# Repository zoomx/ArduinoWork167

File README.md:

# ArduinoWork167
Arduino sketches

Various Arduino Sketches

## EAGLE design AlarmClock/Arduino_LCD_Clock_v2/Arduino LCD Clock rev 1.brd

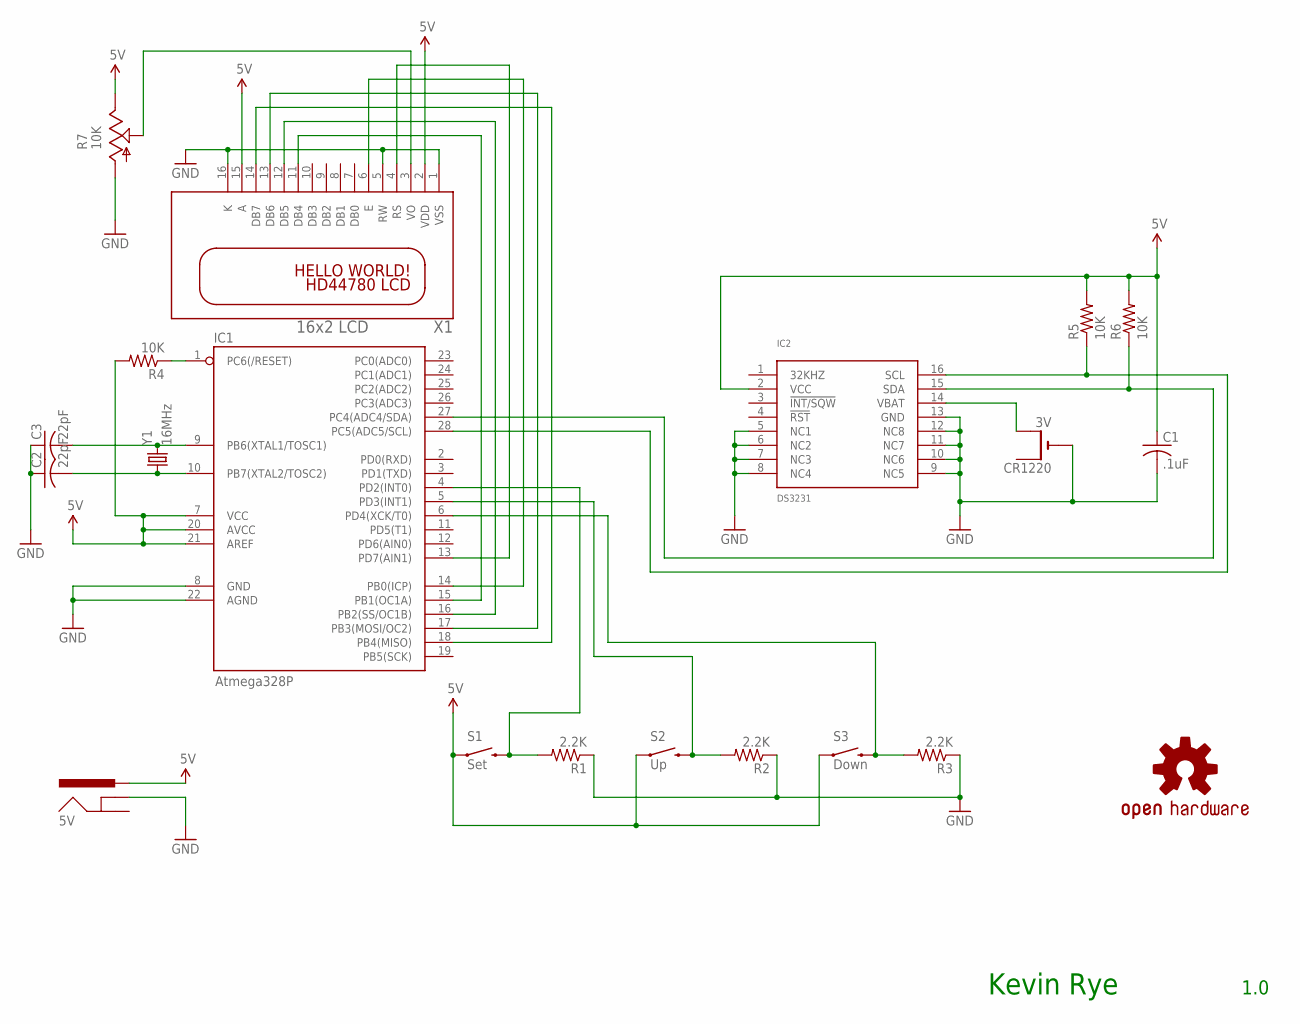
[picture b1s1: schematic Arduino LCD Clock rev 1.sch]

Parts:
5V: POWER_JACKSLT; POWER_JACK_SLOT
C1: .1uF; C025-024X044
C2, C3: 22pF; C025-024X044
CR1220: 3V; CR1220-THM
IC1: Atmega328P; DIL28-3
IC2: DS3231; SO16W
R1, R2, R3: 2.2K; AXIAL-0.4
R4, R5, R6: 10K; AXIAL-0.4
R7: 10K; S63S
S1: Set; TACTILE-PTH-12MM
S2: Up; TACTILE-PTH-12MM
S3: Down; TACTILE-PTH-12MM
U$2: OSHW-LOGOM; OSHW-LOGO-M
X1: 16x2 LCD; LCD1602
Y1: 16MHz; HC49US

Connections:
5V: 5V.PWR, C1.1, IC1.7 (VCC), IC1.20 (AVCC), IC1.21 (AREF), IC2.2 (VCC), R4.P$2 (2), R5.P$2 (2), R6.P$2 (2), R7.E, S1.1, S2.1, S3.1, X1.2 (VDD), X1.15 (A)
GND: 5V.GND@1 (GNDBREAK), C1.2, C2.1, C3.1, CR1220.-, IC1.8 (GND), IC1.22 (AGND), IC2.5 (NC1), IC2.6 (NC2), IC2.7 (NC3), IC2.8 (NC4), IC2.9 (NC5), IC2.10 (NC6), IC2.11 (NC7), IC2.12 (NC8), IC2.13 (GND), R1.P$1 (1), R2.P$1 (1), R3.P$1 (1), R7.A, X1.1 (VSS), X1.5 (RW), X1.16 (K)
unnamed: CR1220.+2 (+1), IC2.14 (VBAT)
unnamed: IC1.18 (PB4(MISO)), X1.14 (DB7)
unnamed: IC1.17 (PB3(MOSI/OC2)), X1.13 (DB6)
unnamed: IC1.28 (PC5(ADC5/SCL)), IC2.16 (SCL), R5.P$1 (1)
unnamed: IC1.13 (PD7(AIN1)), X1.4 (RS)
unnamed: C3.2, IC1.9 (PB6(XTAL1/TOSC1)), Y1.2
unnamed: C2.2, IC1.10 (PB7(XTAL2/TOSC2)), Y1.1
unnamed: IC1.1 (PC6(/RESET)), R4.P$1 (1)
unnamed: R7.S, X1.3 (VO)
unnamed: IC1.14 (PB0(ICP)), X1.6 (E)
unnamed: IC1.16 (PB2(SS/OC1B)), X1.12 (DB5)
unnamed: IC1.15 (PB1(OC1A)), X1.11 (DB4)
unnamed: IC1.5 (PD3(INT1)), R2.P$2 (2), S2.3 (2)
unnamed: IC1.27 (PC4(ADC4/SDA)), IC2.15 (SDA), R6.P$1 (1)
unnamed: IC1.4 (PD2(INT0)), R1.P$2 (2), S1.3 (2)
unnamed: IC1.6 (PD4(XCK/T0)), R3.P$2 (2), S3.3 (2)

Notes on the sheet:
1.0
Kevin Rye

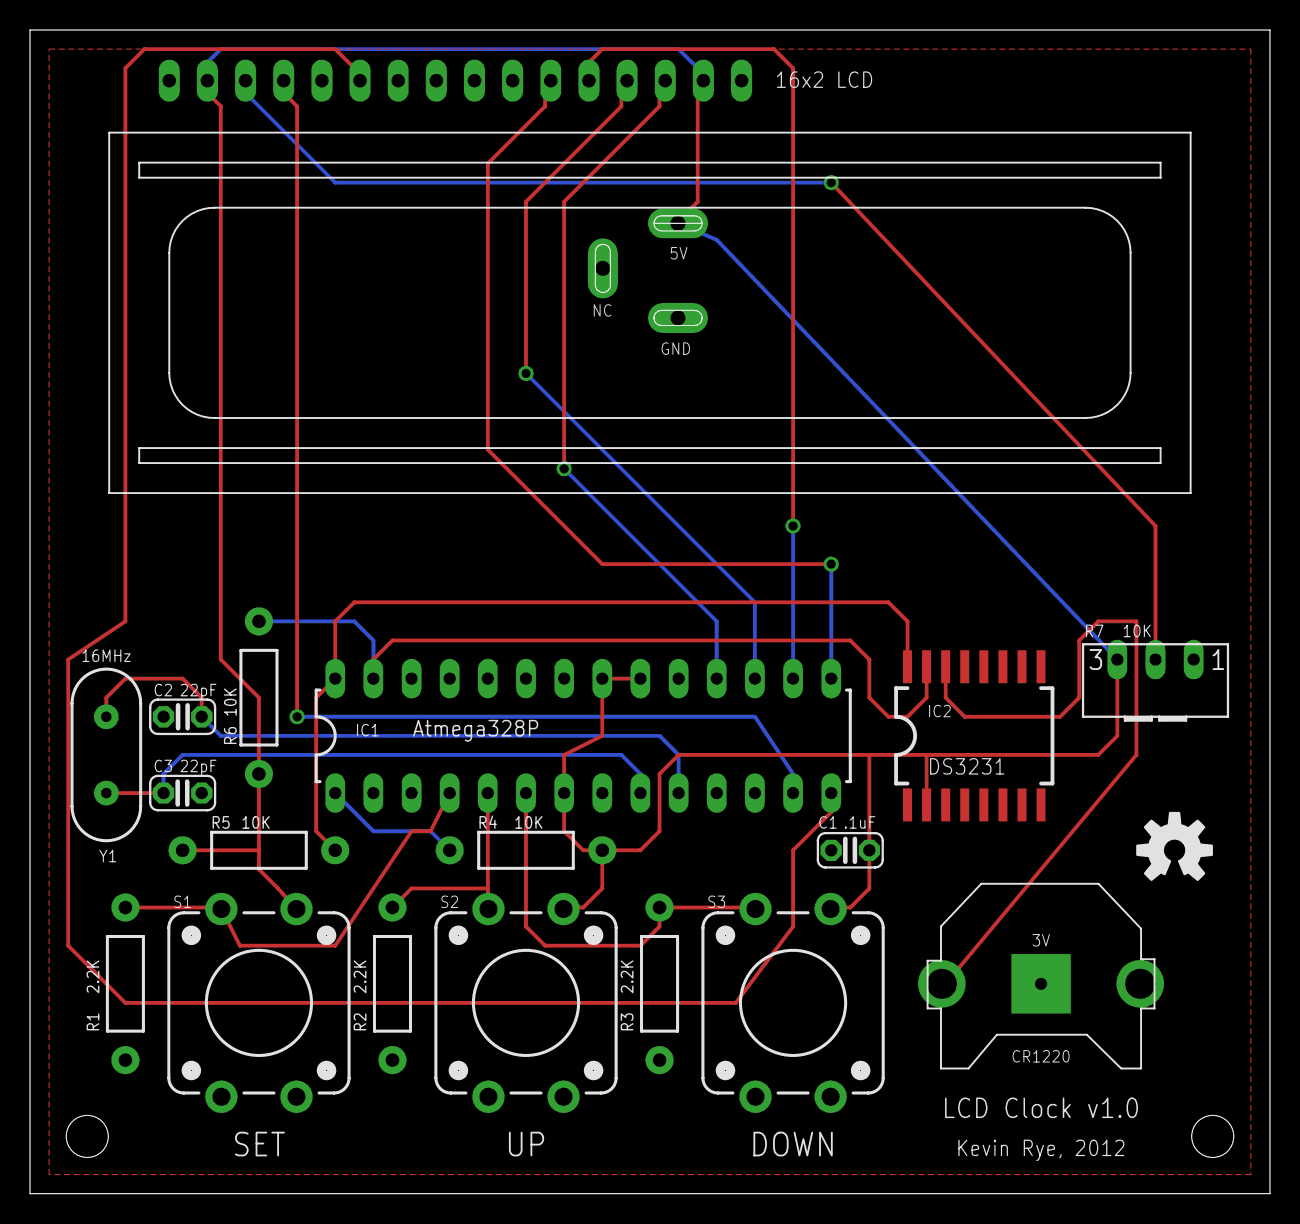
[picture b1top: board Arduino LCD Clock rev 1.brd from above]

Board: 2 copper layers, 82.5 x 77.5 mm, 20 parts (1 on the bottom side), 18 nets.

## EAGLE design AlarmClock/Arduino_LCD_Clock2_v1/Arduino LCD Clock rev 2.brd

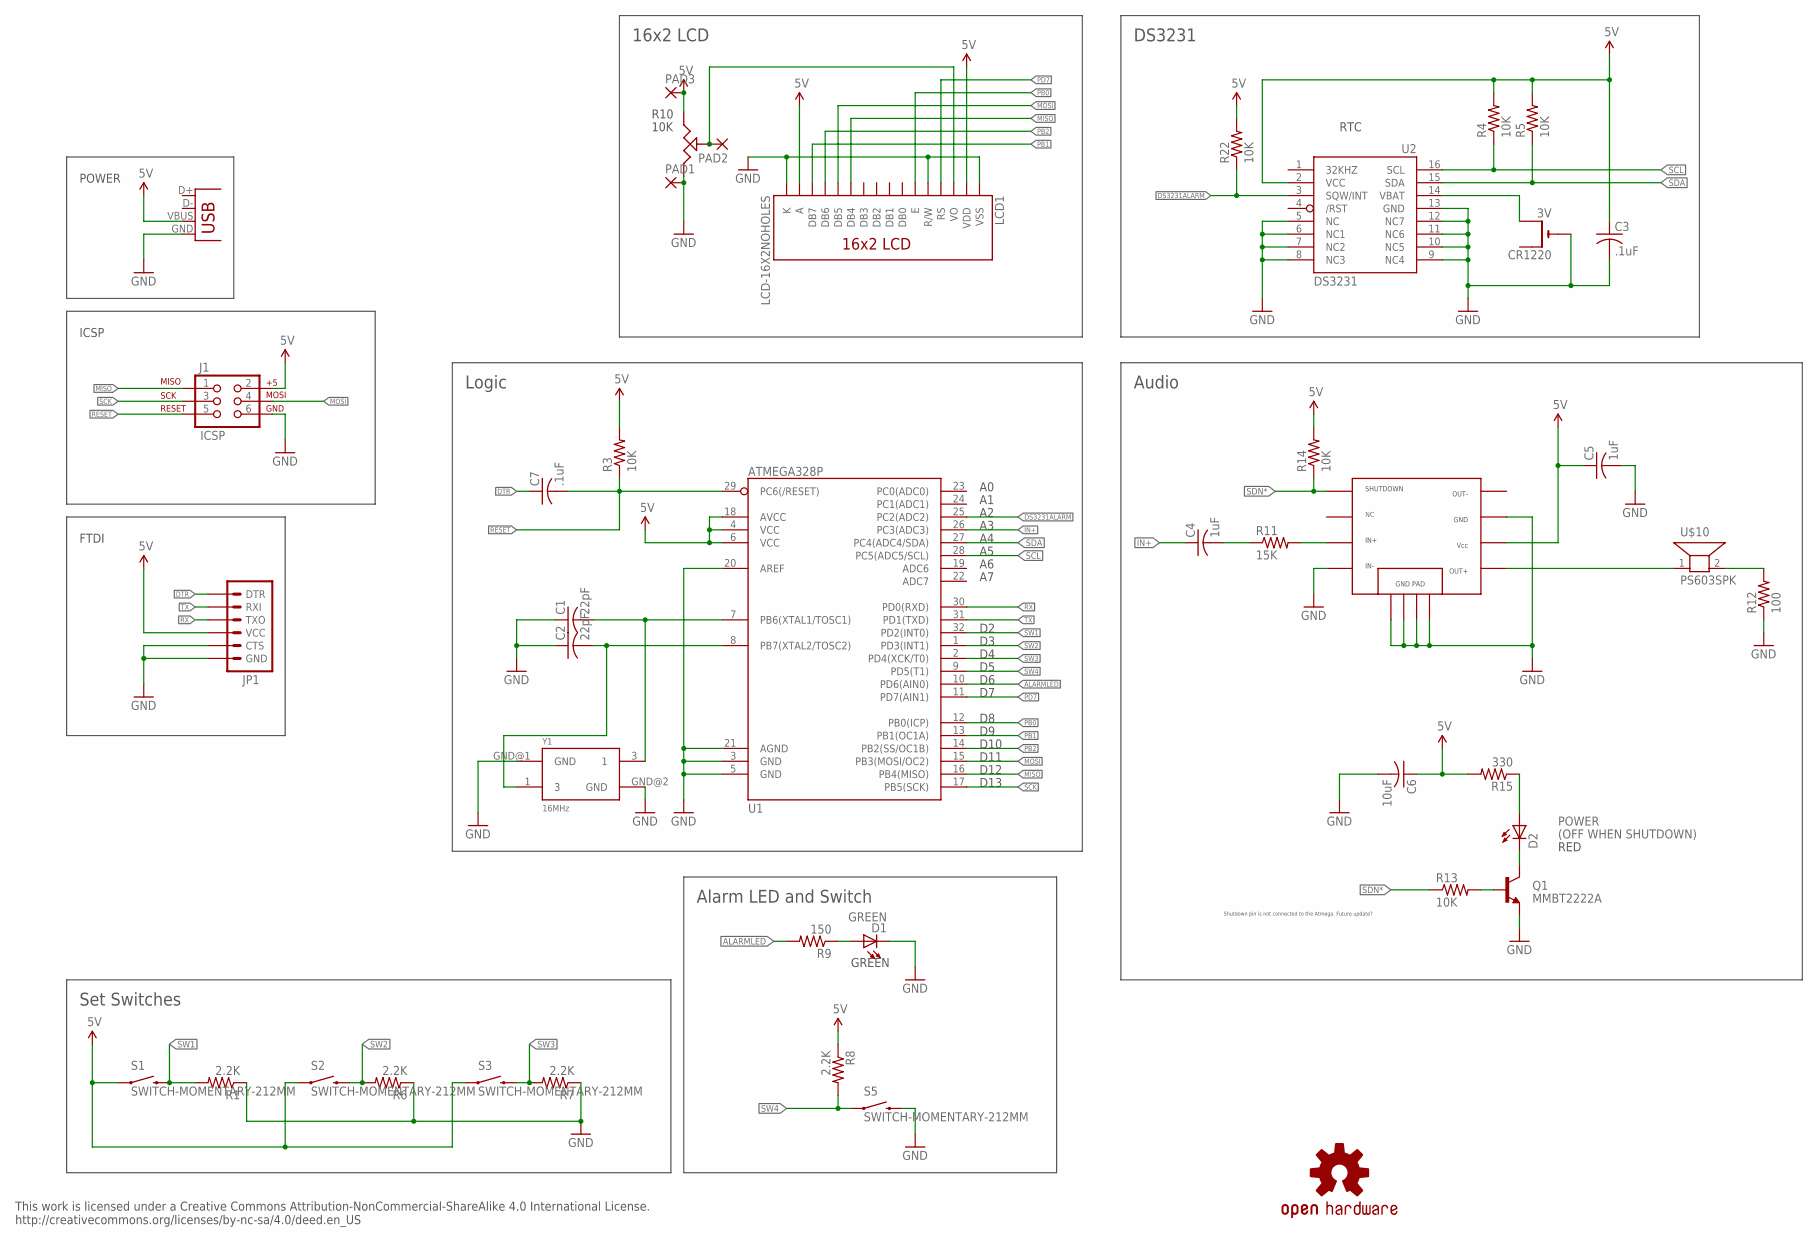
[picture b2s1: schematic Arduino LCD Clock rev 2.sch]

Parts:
C1, C2: 22pF; C0805K
C3, C7: .1uF; C0805K
C4, C5: 1uF; C0805K
C6: 10uF; C0805K
CR1220: 3V; CR1220-THM
D1: GREEN; LED-1206
D2: LED-RED1206; LED-1206
J1: ICSP; 2X3
JP1: ARDUINO_SERIAL_PROGRAMSMD; 1X06-SMD
JP3: (POWER ONLY); USB-B-PTH-VERTICAL
LCD1: LCD-16X2NOHOLES; LCD-16X2_NOHOLES
PAD1, PAD2, PAD3: SMD2; SMD1,27-2,54
Q1: MMBT2222A; SOT23-3
R1, R6, R7, R8: 2.2K; R0805
R3, R4, R5, R13, R14, R22: 10K; R0805
R9: 150; R0805
R11: 15K; R0805
R12: 100; R0805
R15: 330; R0805
S1, S2, S3, S5: SWITCH-MOMENTARY-212MM; TACTILE-PTH-12MM
U1: ATMEGA328P; TQFP32-08
U2: DS3231; SO16W
U3: TPA2005; MSOP8
U$2: OSHW-LOGOM; OSHW-LOGO-M
U$6: PVG3A103C01R00_TRIMPOT
U$10: PS603SPK; PS603
Y1: 16MHz; CRYSTAL-SMD-5X3

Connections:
5V: C3.1, C5.1, C6.1, J1.2, JP1.4 (VCC), JP3.VBUS, LCD1.2 (VDD), LCD1.15 (A), PAD3.1, R3.2, R4.2, R5.2, R8.1, R14.2, R15.2, R22.2, S1.1, S2.1, S3.1, U1.4 (VCC), U1.6 (VCC), U1.18 (AVCC), U2.2 (VCC), U3.6, U$6.1 (IN), U$6.1$ (IN)
ALARMLED: R9.2, U1.10 (PD6(AIN0))
DS3231ALARM: R22.1, U1.25 (PC2(ADC2)), U2.3 (SQW/INT)
DTR: C7.1, JP1.1 (DTR)
GND: C1.1, C2.1, C3.2, C5.2, C6.2, CR1220.-, D1.C, J1.6, JP1.5 (CTS), JP1.6 (GND), JP3.GND, LCD1.1 (VSS), LCD1.5 (R/W), LCD1.16 (K), PAD1.1, Q1.2 (E), R1.1, R6.1, R7.1, R12.1, S5.3 (2), U1.3 (GND), U1.5 (GND), U1.20 (AREF), U1.21 (AGND), U2.5 (NC), U2.6 (NC1), U2.7 (NC2), U2.8 (NC3), U2.9 (NC4), U2.10 (NC5), U2.11 (NC6), U2.12 (NC7), U2.13 (GND), U3.4, U3.7, U3.A, U3.B, U3.C, U3.D, U$6.3 (GND), U$6.3$ (GND), Y1.GND@1 (GND), Y1.GND@2 (GND)
IN+: C4.1, U1.26 (PC3(ADC3))
IN+AMP: R11.2, U3.3
MISO: J1.1, LCD1.11 (DB4), U1.16 (PB4(MISO))
MOSI: J1.4, LCD1.12 (DB5), U1.15 (PB3(MOSI/OC2))
unnamed: CR1220.+2 (+1), U2.14 (VBAT)
unnamed: U3.5, U$10.1
unnamed: LCD1.3 (VO), PAD2.1, U$6.2 (OUT), U$6.2! (OUT)
unnamed: R12.2, U$10.2
unnamed: D1.A, R9.1
unnamed: D2.A, R15.1
unnamed: Q1.1 (B), R13.2
unnamed: D2.C, Q1.3 (C)
unnamed: C4.2, R11.1
unnamed: C1.2, U1.7 (PB6(XTAL1/TOSC1)), Y1.3 (1)
unnamed: C2.2, U1.8 (PB7(XTAL2/TOSC2)), Y1.1 (3)
PB0: LCD1.6 (E), U1.12 (PB0(ICP))
PB1: LCD1.14 (DB7), U1.13 (PB1(OC1A))
PB2: LCD1.13 (DB6), U1.14 (PB2(SS/OC1B))
PD7: LCD1.4 (RS), U1.11 (PD7(AIN1))
RESET: C7.2, J1.5, R3.1, U1.29 (PC6(/RESET))
RX: JP1.3 (TXO), U1.30 (PD0(RXD))
SCK: J1.3, U1.17 (PB5(SCK))
SCL: R4.1, U1.28 (PC5(ADC5/SCL)), U2.16 (SCL)
SDA: R5.1, U1.27 (PC4(ADC4/SDA)), U2.15 (SDA)
SDN*: R13.1, R14.1, U3.1
SW1: R1.2, S1.3 (2), U1.32 (PD2(INT0))
SW2: R6.2, S2.3 (2), U1.1 (PD3(INT1))
SW3: R7.2, S3.3 (2), U1.2 (PD4(XCK/T0))
SW4: R8.2, S5.1, U1.9 (PD5(T1))
TX: JP1.2 (RXI), U1.31 (PD1(TXD))

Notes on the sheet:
RTC
POWER
(OFF WHEN SHUTDOWN)
Audio
Set Switches
DS3231
Alarm LED and Switch
16x2 LCD
FTDI
ICSP
D10
D11
D12
D13
Logic
GREEN
RED
10K
R10
This work is licensed under a Creative Commons Attribution-NonCommercial-ShareAlike 4.0 International License. http://creativecommons.org/licenses/by-nc-sa/4.0/deed.en_US
Shutdown pin is not connected to the Atmega. Future update?

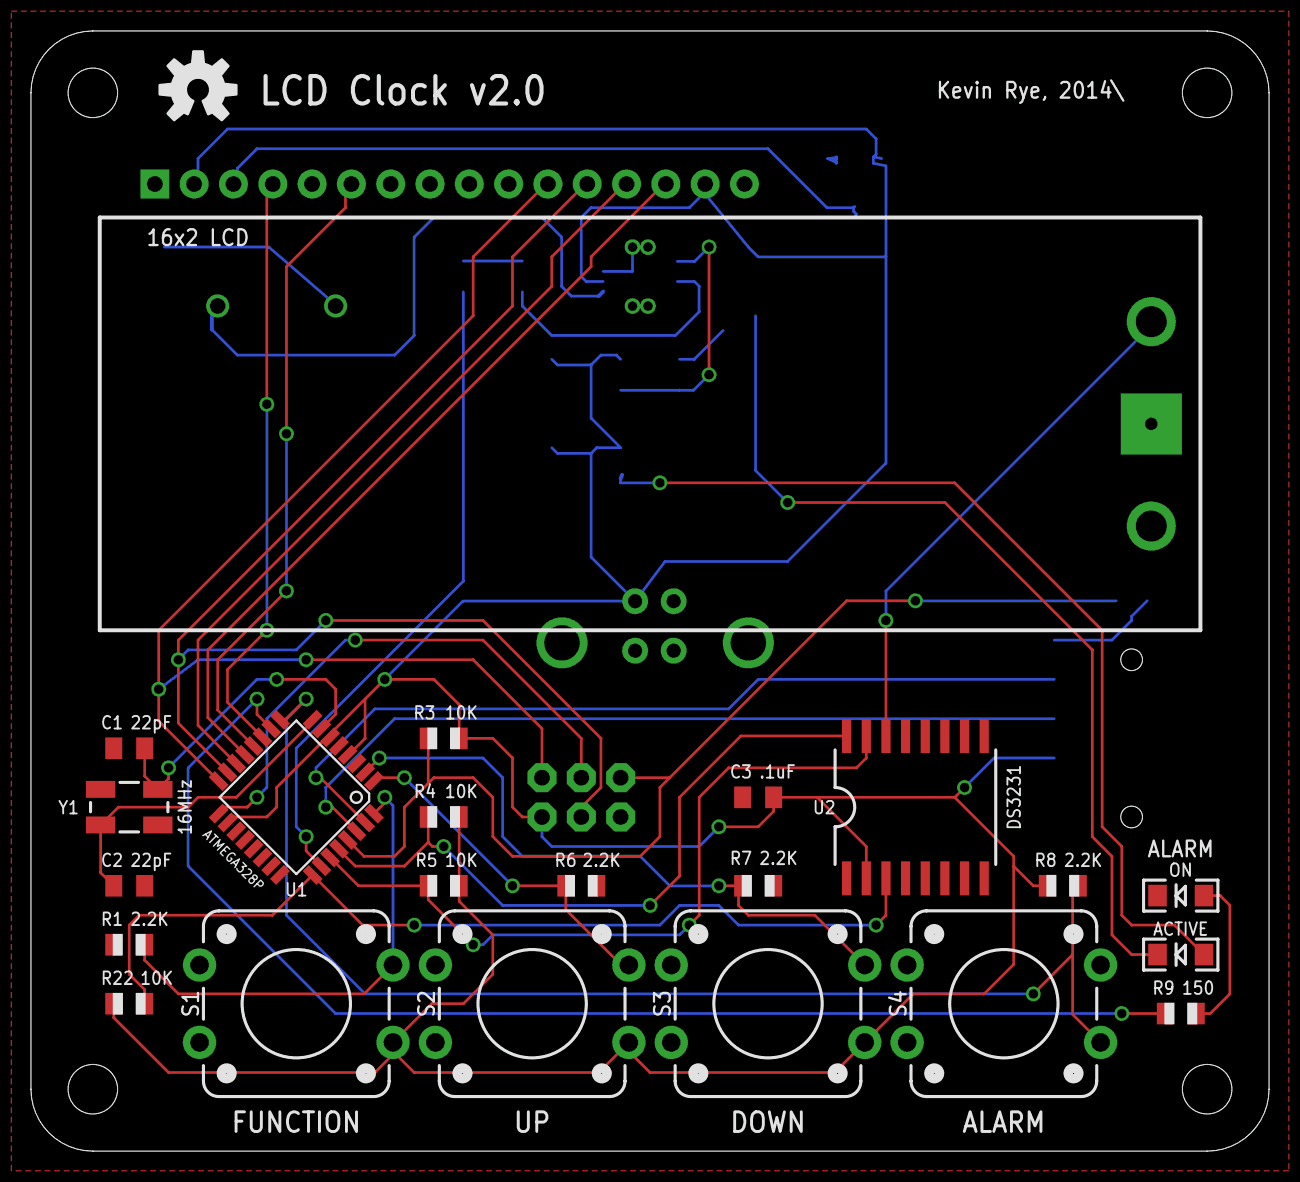
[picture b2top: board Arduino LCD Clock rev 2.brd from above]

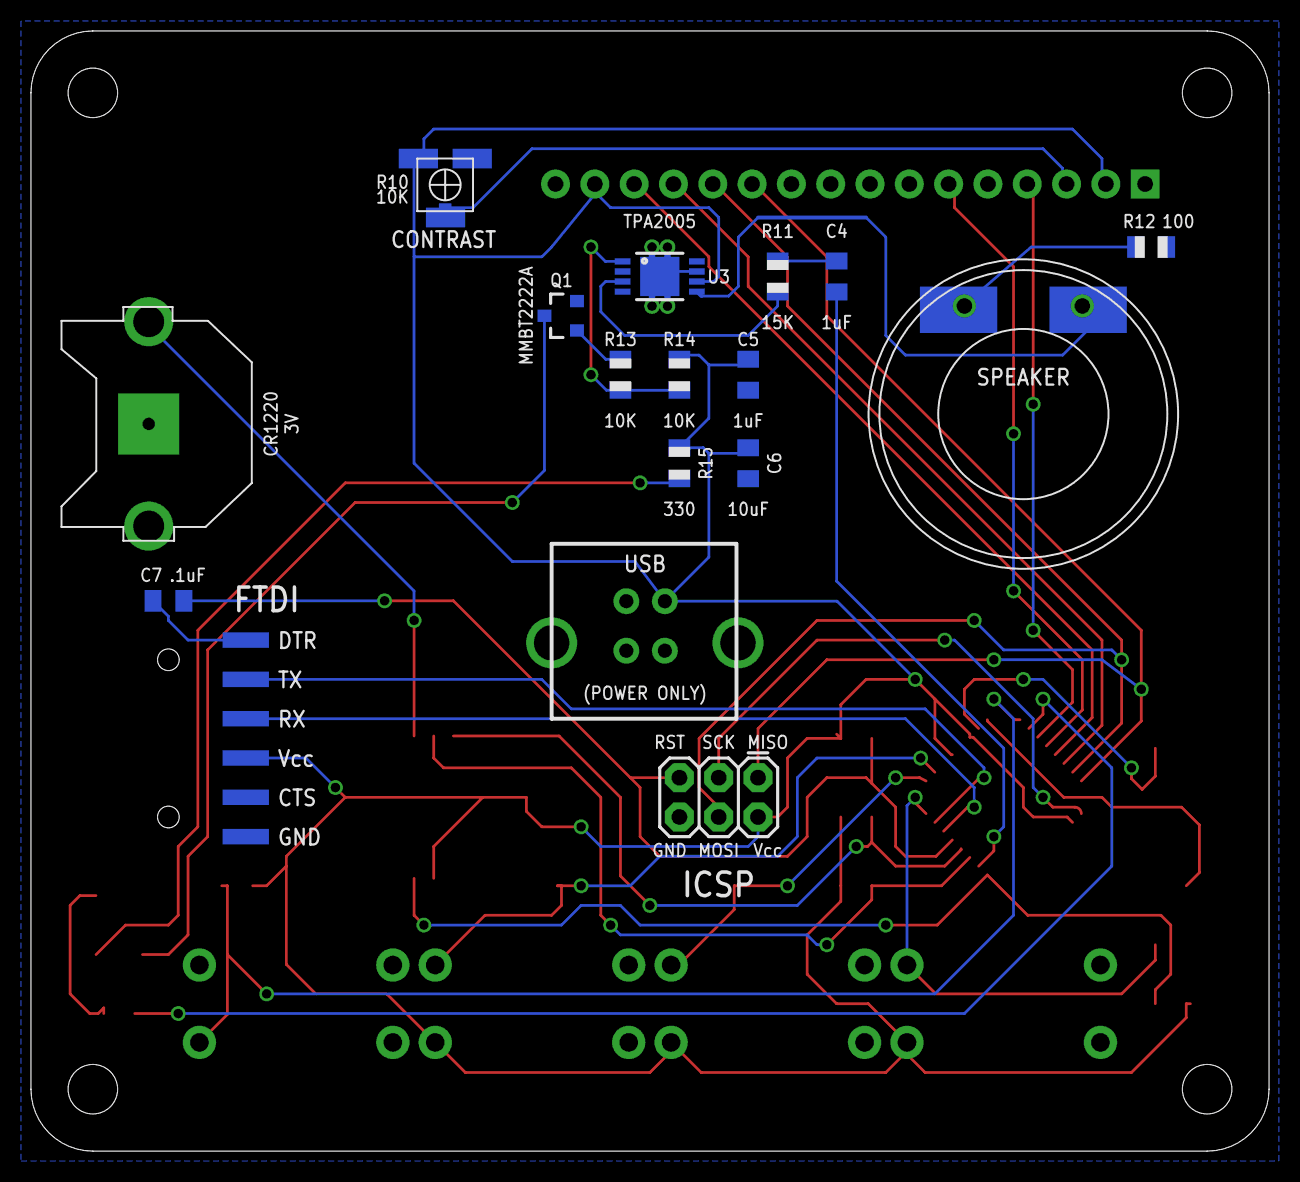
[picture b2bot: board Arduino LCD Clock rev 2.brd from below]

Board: 2 copper layers, 80.0 x 72.4 mm, 44 parts (20 on the bottom side), 35 nets.

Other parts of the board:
U$5: LCD_V2_FOOTPRINT

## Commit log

2016-03-10 Added files via upload
2016-03-10 Added libraries
2016-03-14 Added some comments
2016-03-15 Software serial pins changed
    Software serial pins changed to 2 and 3
2016-03-17 Initial code
2016-03-17 Some changes but no voice
2016-03-18 Added comment that doesn't work
    Doesn't work because PCM is on Pin 11 used by MISO for SPI communication with Ethernet card
2016-03-18 This one works.
2016-03-21 Added Alarm
    Added an alarm when CO2 is more than a value. Some libraries are now in the same sketch folder.
2016-07-22 Add files via upload
    Added NRF24Sensors Sketches
2016-10-20 Added one shield test
    Added Quad_Relay_Shield_test
2016-10-21 Original Rude Bastard Sketch
    taken from http://www.rudebastard.com/article.php?story=20130310155336385
2016-10-21 My modifications
    My modifications
2016-10-21 Now 0 mean relay off
    Changed the logic since in the original sketch was negate
    Now 0 mean relay off
2016-10-21 Corrected silly error on readme
    logis is now logic!
2016-10-21 Added mask and gateway for fixed IP
2016-11-02 First version
2016-11-02 Version 01b
2016-11-02 Version 01c
2016-11-02 Added DHT11 library
2016-11-02 Version 01d
2016-11-02 Version 01e
2016-11-02 Added XPFM 115kpa test
2016-11-02 Added TSL2561 test
2016-11-02 Added TSL2561 library
2016-11-02 Added TM7709 24 bit ADC module test
2016-11-02 Added TCS230 board test
2016-11-02 Added LTC2400 24bit ADC Module test
2016-11-02 Added KY_013 module thermistor test
2017-03-22 Added SerialRelayControl
2017-03-22 Temperature control is checked with millis delay
    Temperature control is checked with millis delay and others small changes.
2017-03-30 Added SolarTracker01
    Got here http://www.electronicshub.org/arduino-solar-tracker/
2017-03-30 Added comments and serial prints
2017-03-30 Added Thermorecorder
2017-04-03 Added SerialThermo example with millis instead of delay
2017-04-03 Added Thermopcouple code and use of millis
2020-03-30 Wind data corrected, added negative temperatures

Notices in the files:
parts and their libraries:
SparkFun-LED: Licensing: CC v3.0 Share-Alike You are welcome to use this library for commercial purposes.
